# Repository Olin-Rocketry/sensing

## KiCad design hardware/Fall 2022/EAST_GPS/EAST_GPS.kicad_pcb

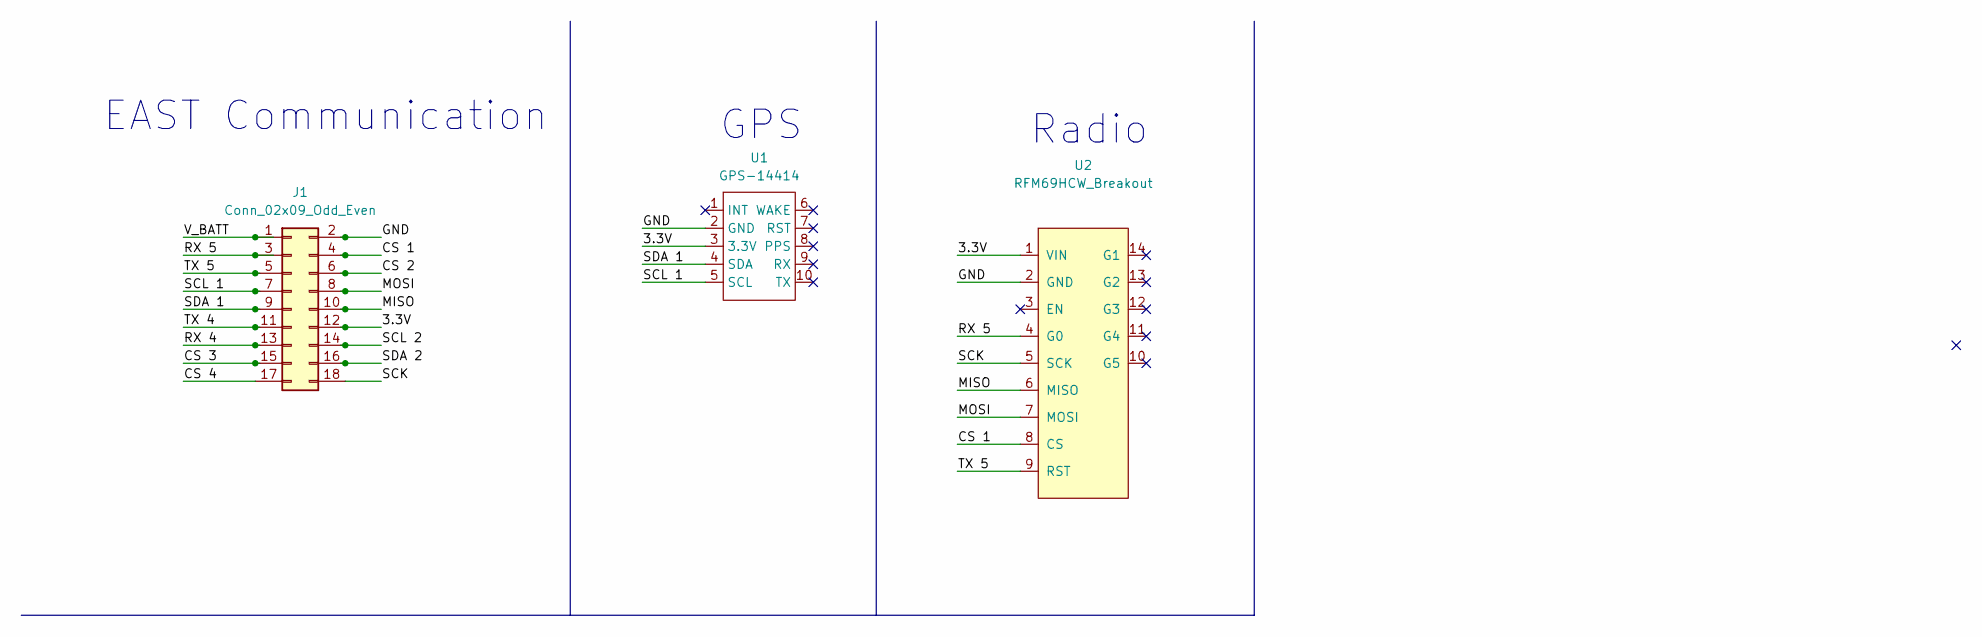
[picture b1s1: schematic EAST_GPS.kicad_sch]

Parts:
J1: Conn_02x09_Odd_Even; PinHeader_2x09_P2.54mm_Vertical
U1: GPS-14414
U2: RFM69HCW_Breakout

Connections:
/3.3V: J1.12, U1.3 (3.3V), U2.1 (VIN)
/CS 1: J1.4, U2.8 (CS)
/CS 2: J1.6
/CS 3: J1.15
/CS 4: J1.17
/GND: J1.2, U1.2 (GND), U2.2 (GND)
/MISO: J1.10, U2.6 (MISO)
/MOSI: J1.8, U2.7 (MOSI)
/RX 4: J1.13
/RX 5: J1.3, U2.4 (G0)
/SCK: J1.18, U2.5 (SCK)
/SCL 1: J1.7, U1.5 (SCL)
/SCL 2: J1.14
/SDA 1: J1.9, U1.4 (SDA)
/SDA 2: J1.16
/TX 4: J1.11
/TX 5: J1.5, U2.9 (RST)
/V_BATT: J1.1

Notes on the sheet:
EAST Communication
Radio
GPS

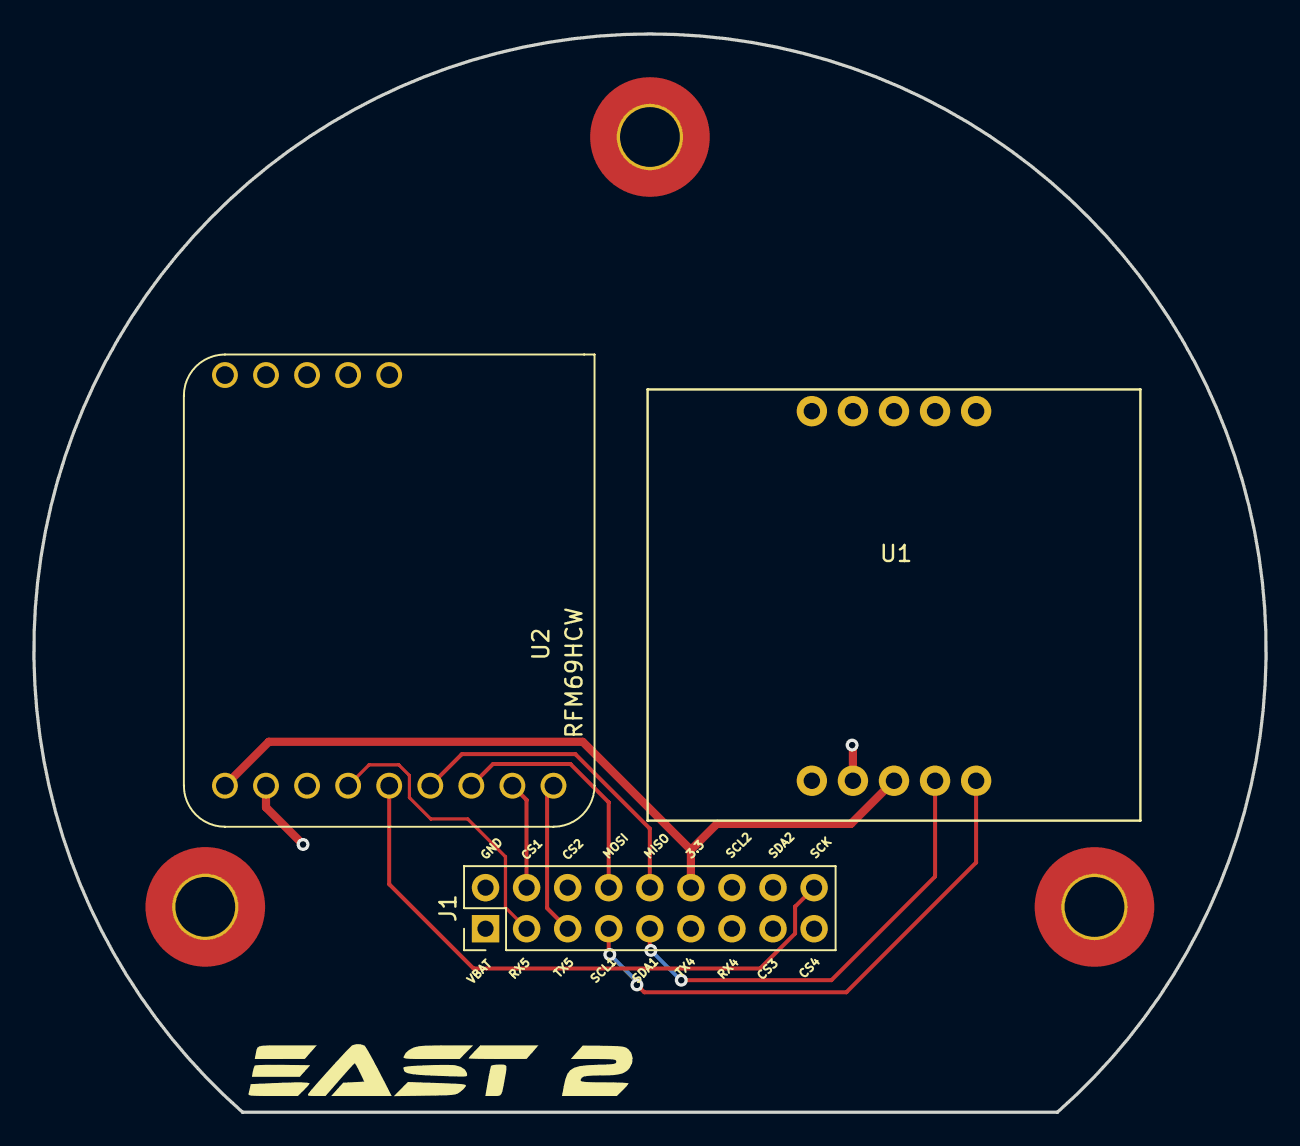
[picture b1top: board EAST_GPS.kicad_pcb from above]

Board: 2 copper layers, 76.2 x 66.7 mm, 3 parts (1 on the bottom side), 10 nets.

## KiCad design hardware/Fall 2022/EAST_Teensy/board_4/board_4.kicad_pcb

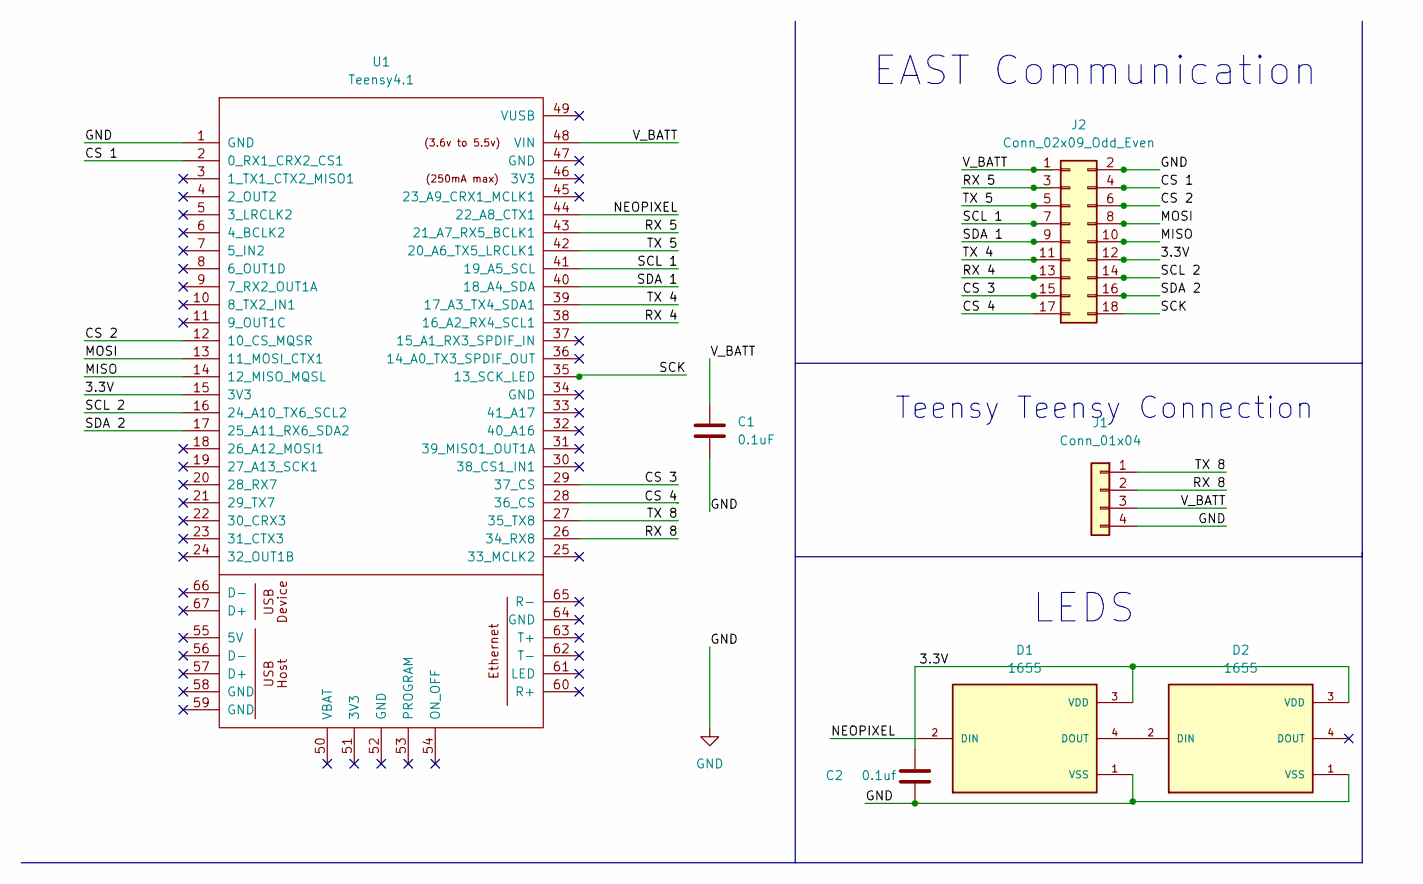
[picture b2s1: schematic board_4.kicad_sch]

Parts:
C1: 0.1uF; C_0603_1608Metric
C2: 0.1uf; C_0603_1608Metric
D1, D2: 1655; LED_1655; PARTREV 01
J1: Conn_01x04; JST_PH_S4B-PH-K_1x04_P2.00mm_Horizontal
J2: Conn_02x09_Odd_Even; PinHeader_2x09_P2.54mm_Vertical
U1: Teensy4.1; Teensy41

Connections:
/3.3V: C2.2, D1.3 (VDD), D2.3 (VDD), J2.12, U1.15 (3V3)
/CS 1: J2.4, U1.2 (0_RX1_CRX2_CS1)
/CS 2: J2.6, U1.12 (10_CS_MQSR)
/CS 3: J2.15, U1.29 (37_CS)
/CS 4: J2.17, U1.28 (36_CS)
/MISO: J2.10, U1.14 (12_MISO_MQSL)
/MOSI: J2.8, U1.13 (11_MOSI_CTX1)
/NEOPIXEL: D1.2 (DIN), U1.44 (22_A8_CTX1)
/RX 4: J2.13, U1.38 (16_A2_RX4_SCL1)
/RX 5: J2.3, U1.43 (21_A7_RX5_BCLK1)
/RX 8: J1.2, U1.26 (34_RX8)
/SCK: J2.18, U1.35 (13_SCK_LED)
/SCL 1: J2.7, U1.41 (19_A5_SCL)
/SCL 2: J2.14, U1.16 (24_A10_TX6_SCL2)
/SDA 1: J2.9, U1.40 (18_A4_SDA)
/SDA 2: J2.16, U1.17 (25_A11_RX6_SDA2)
/TX 4: J2.11, U1.39 (17_A3_TX4_SDA1)
/TX 5: J2.5, U1.42 (20_A6_TX5_LRCLK1)
/TX 8: J1.1, U1.27 (35_TX8)
/V_BATT: C1.1, J1.3, J2.1, U1.48 (VIN)
GND: C1.2, C2.1, D1.1 (VSS), D2.1 (VSS), J1.4, J2.2, U1.1 (GND)
unnamed: D1.4 (DOUT), D2.2 (DIN)

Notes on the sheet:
LEDS
Teensy Teensy Connection
EAST Communication

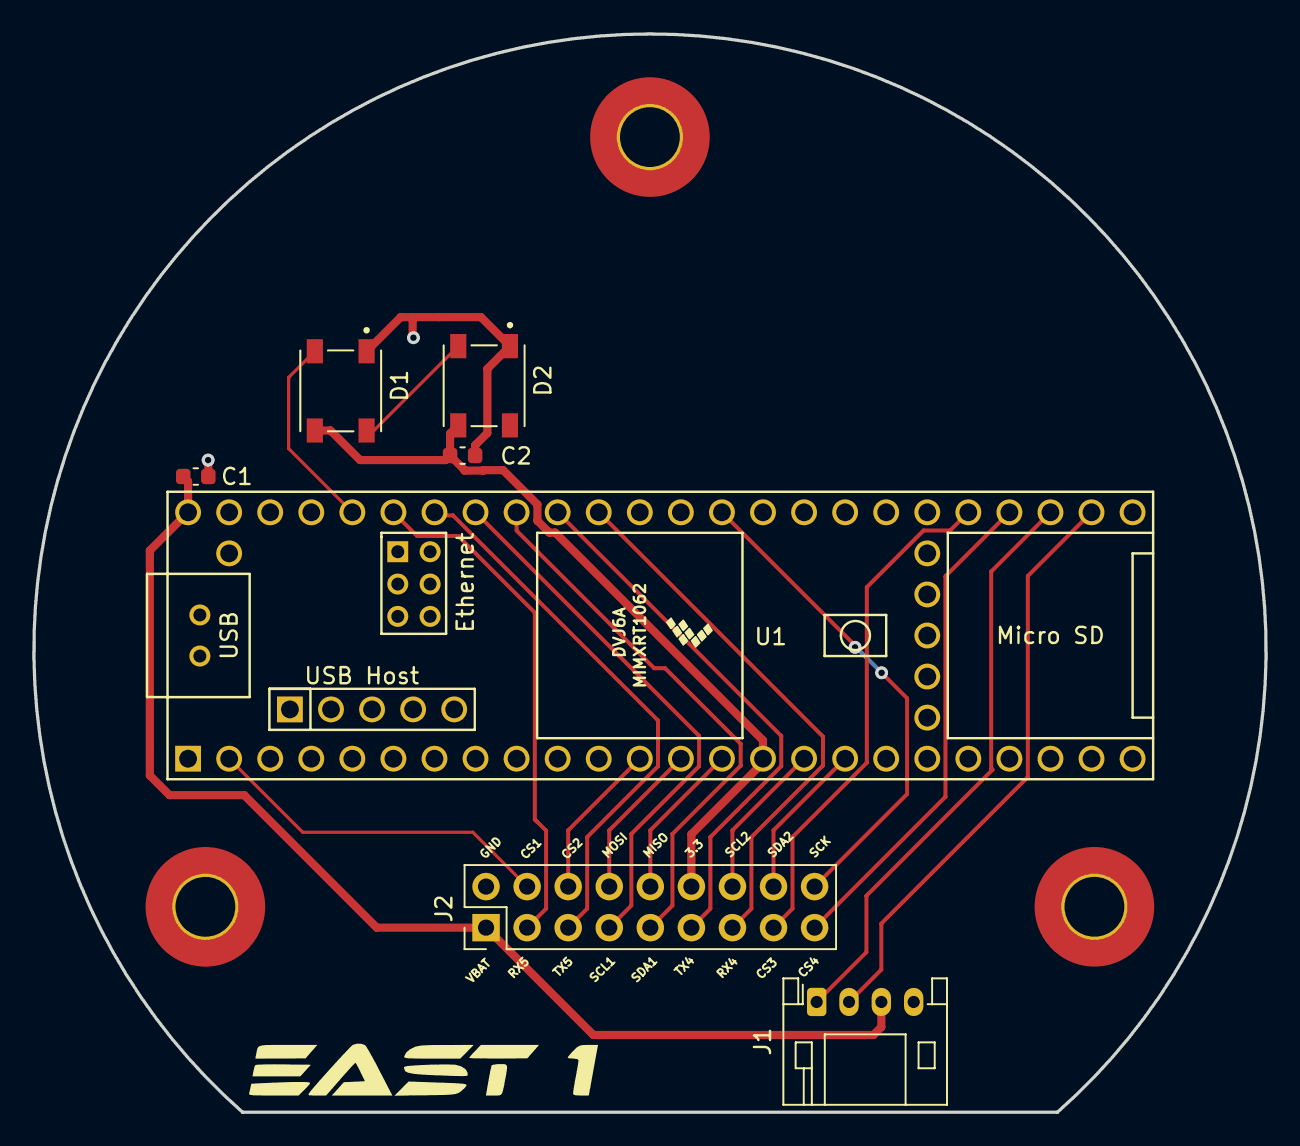
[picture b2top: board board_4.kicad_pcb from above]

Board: 2 copper layers, 76.2 x 66.7 mm, 7 parts (0 on the bottom side), 22 nets.

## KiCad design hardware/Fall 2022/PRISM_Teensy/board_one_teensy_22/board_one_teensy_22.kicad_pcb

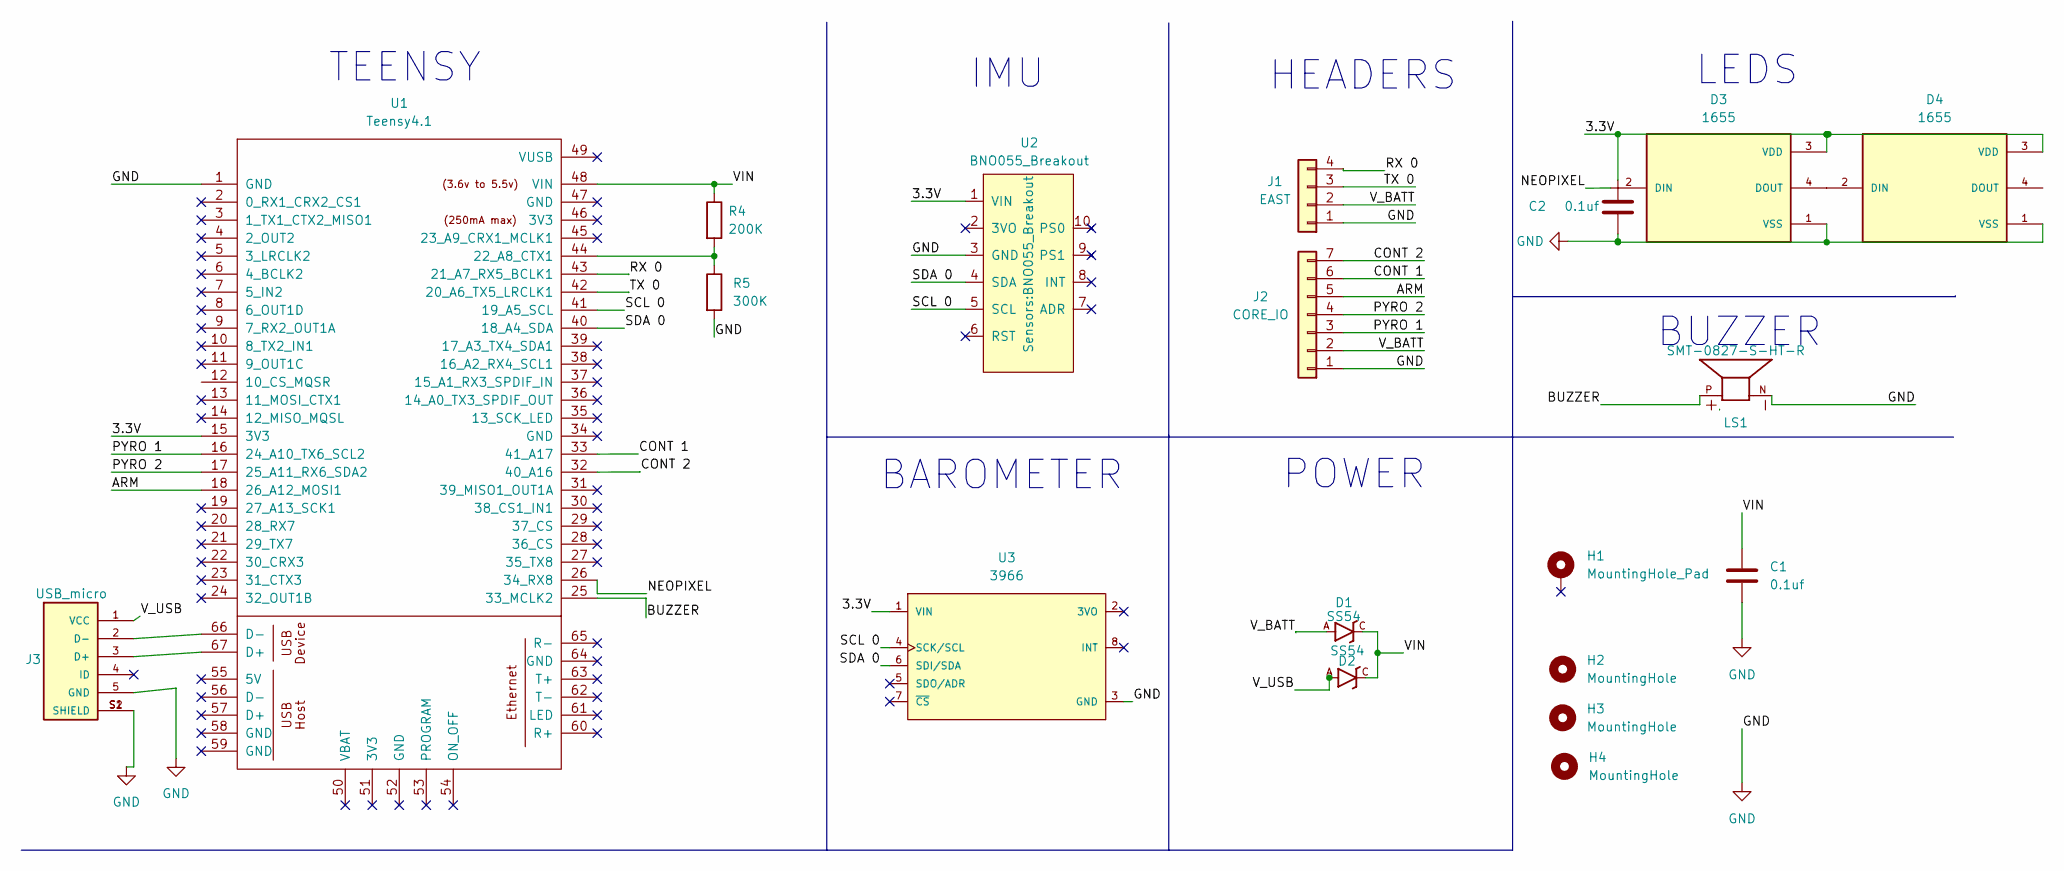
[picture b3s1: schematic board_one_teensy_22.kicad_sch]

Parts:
C1, C2: 0.1uf; C_0603_1608Metric
D1, D2: SS54; DO-214AC
D3, D4: 1655; LED_1655; PARTREV 01
H1: MountingHole_Pad; MountingHole_3.2mm_M3_DIN965_Pad_TopBottom
H2, H3, H4: MountingHole; MountingHole_3.2mm_M3_DIN965_Pad_TopBottom
J1: EAST; JST_PH_S4B-PH-K_1x04_P2.00mm_Horizontal
J2: CORE_IO; JST_PH_S7B-PH-K_1x07_P2.00mm_Horizontal
J3: USB_micro; GCT_USB3131-30-0230-A_REVB
LS1: SMT-0827-S-HT-R; XDCR_SMT-0827-S-HT-R; PARTREV 31/03/20
R4: 200K; R_0603_1608Metric
R5: 300K; R_0603_1608Metric
U1: Teensy4.1; Teensy41
U2: BNO055_Breakout
U3: 3966; Adafruit_Industries-3966-MFG; mouser part number 485-3966; digikey description BMP388 - PRECISION BAROMETRIC PR

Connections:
/3.3V: C2.2, D3.3 (VDD), D4.3 (VDD), U1.15 (3V3), U2.1 (VIN), U3.1 (VIN)
/ARM: J2.5, U1.18 (26_A12_MOSI1)
/BUZZER: LS1.P, U1.25 (33_MCLK2)
/CONT 1: J2.6, U1.33 (41_A17)
/CONT 2: J2.7, U1.32 (40_A16)
/NEOPIXEL: D3.2 (DIN), U1.26 (34_RX8)
/PYRO 1: J2.3, U1.16 (24_A10_TX6_SCL2)
/PYRO 2: J2.4, U1.17 (25_A11_RX6_SDA2)
/RX 0: J1.4, U1.43 (21_A7_RX5_BCLK1)
/SCL 0: U1.41 (19_A5_SCL), U2.5 (SCL), U3.4 (SCK/SCL)
/SDA 0: U1.40 (18_A4_SDA), U2.4 (SDA), U3.6 (SDI/SDA)
/TX 0: J1.3, U1.42 (20_A6_TX5_LRCLK1)
/VIN: C1.1, D1.C, D2.C, R4.1, U1.48 (VIN)
/V_BATT: D1.A, J1.2, J2.2
/V_USB: D2.A, J3.1 (VCC)
GND: C1.2, C2.1, D3.1 (VSS), D4.1 (VSS), J1.1, J2.1, J3.5 (GND), J3.S1 (SHIELD), J3.S2 (SHIELD), LS1.N, R5.2, U1.1 (GND), U2.3 (GND), U3.3 (GND)
unnamed: D3.4 (DOUT), D4.2 (DIN)
unnamed: J3.2 (D-), U1.66 (D-)
unnamed: J3.3 (D+), U1.67 (D+)
unnamed: R4.2, R5.1, U1.44 (22_A8_CTX1)

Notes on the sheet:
BUZZER
TEENSY
HEADERS
POWER
LEDS
IMU
BAROMETER

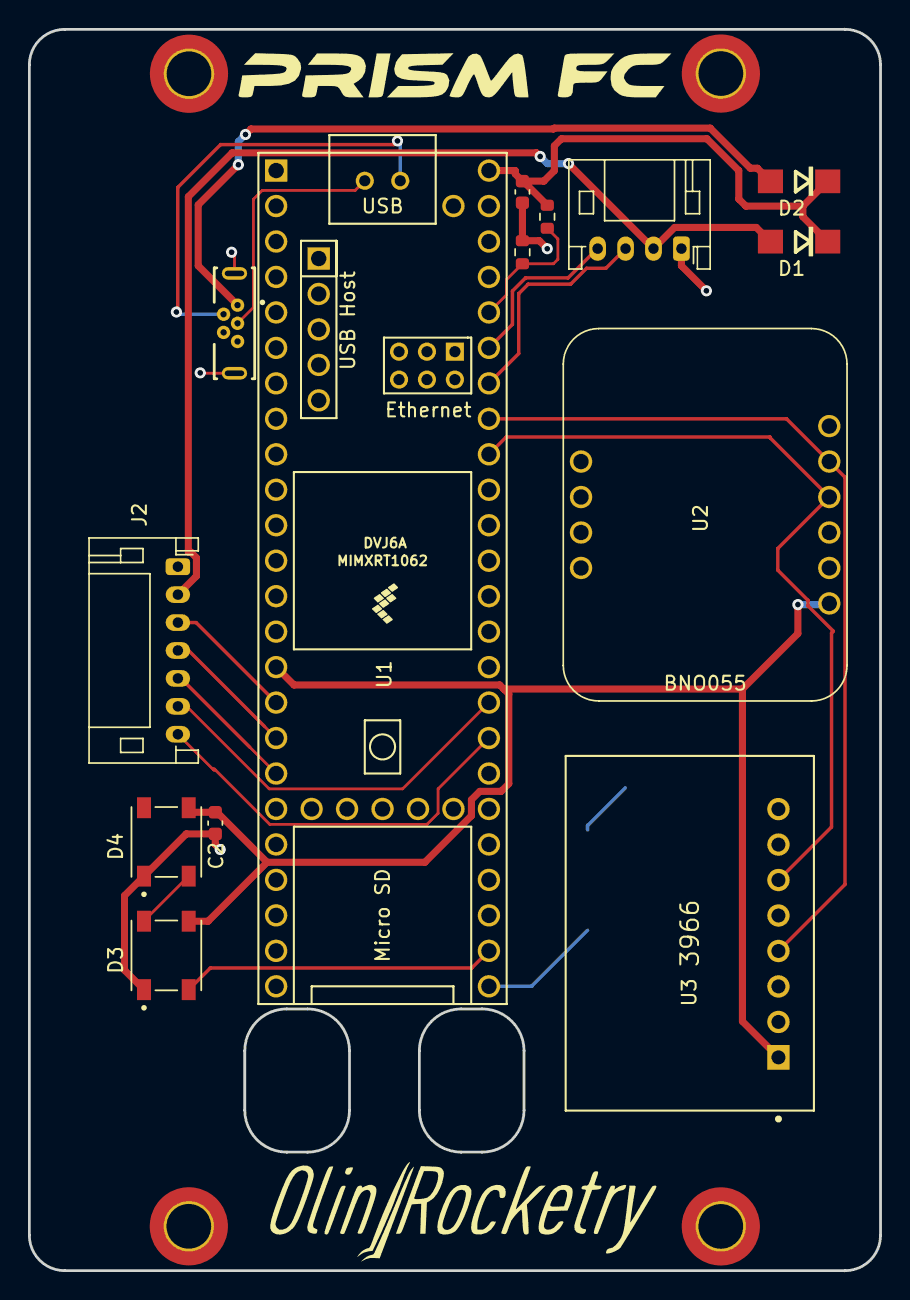
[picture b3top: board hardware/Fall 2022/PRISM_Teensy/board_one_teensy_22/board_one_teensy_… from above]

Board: 2 copper layers, 61.0 x 88.9 mm, 19 parts (1 on the bottom side), 20 nets.

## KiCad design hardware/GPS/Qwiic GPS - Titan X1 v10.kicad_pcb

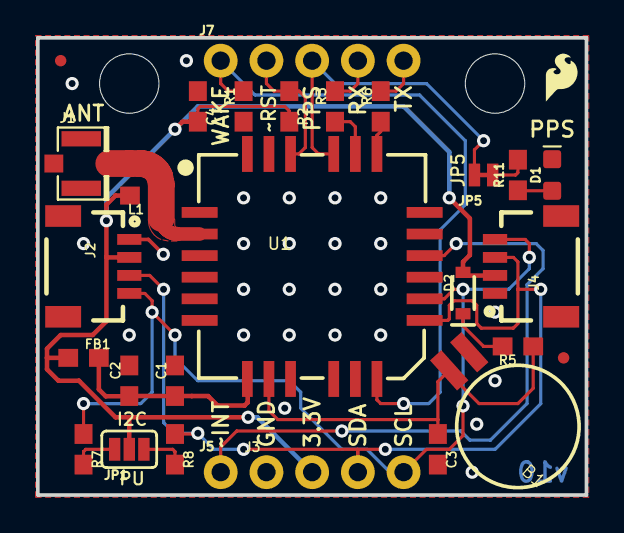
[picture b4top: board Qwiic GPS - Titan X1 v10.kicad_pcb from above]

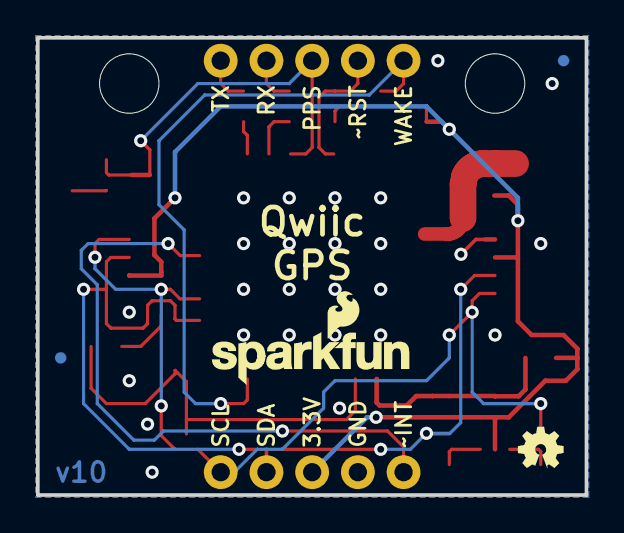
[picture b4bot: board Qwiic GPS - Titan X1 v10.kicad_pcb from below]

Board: 2 copper layers, 30.5 x 25.4 mm, 38 parts (4 on the bottom side), 20 nets.

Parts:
B1: 6.8MM_COIN_CELL; BATTCON-6.8MM
C1: 0.1uF; 0603
C2, C3, C4: 1.0uF; 0603
D1: BLUE; LED-0603
D2: 0.5A/40V/420mV; SOD-323
FB1: 600Ohm/100MHz; 0603
FRAME1: FRAME-LETTER; CREATIVE_COMMONS
J1: U.FL
J2, J4: Qwiic Right Angle; 1X04_1MM_RA
J3: PTH; 1X04_NO_SILK
J5: 1X01_NO_SILK
J7: 1X05_NO_SILK
JP1: SMT-JUMPER_3_2-NC_PASTE_SILK
JP2, JP6, JP7, JP8: FIDUCIALUFIDUCIAL; MICRO-FIDUCIAL
JP3, JP4: STAND-OFF
JP5: SMT-JUMPER_2_NC_TRACE_NO-SILK
L1: 33nH/±5%/500mA; 0603
LOGO1: OSHW-LOGOMINI; OSHW-LOGO-MINI
LOGO2: SFE_LOGO_NAME_FLAME.1_INCH; SFE_LOGO_NAME_FLAME_.1
LOGO3: REVISION
R1, R2: 10k; 0603
R3, R6, R11: 470; 0603
R5: 1k; 0603
R7, R8: 4.7k; 0603
U1: Titan X1 GPS; TITAN_X1_GPS
U$2: SFE_LOGO_FLAME_.1
U$3: SPECIAL_INSTRUCTIONS-PRODUCTION; PRODUCTION_INSTRUCTIONS

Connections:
3.3V: C4.2, D2.A, FB1.1, J2.2, J3.2, J4.2, JP1.2, L1.2, R2.2
BACKUP: B1.+, C3.1, R5.1, U1.8
EXT_ANT: J1.FEED, L1.1, U1.2
GND: B1.-, C1.2, C2.2, C3.2, C4.1, D1.C, J1.1, J1.2, J2.1, J3.1, J4.1, R1.1, U1.1, U1.3, U1.4, U1.5, U1.6, U1.9, U1.10, U1.11, U1.24
INT: J5.1, U1.16
unnamed: D1.A, R11.1
unnamed: JP5.1, R11.2
unnamed: JP1.1, R8.2
unnamed: D2.C, R5.2
unnamed: JP1.3, R7.2
PPS: J7.3, JP5.2, U1.21
RX: J7.4, R3.2
RXLV: R3.1, U1.20
SCL: J2.4, J3.4, J4.4, R7.1, U1.14
SDA: J2.3, J3.3, J4.3, R8.1, U1.13
TX: J7.5, R6.2
TXLV: R6.1, U1.19
VCC_FILTERED: C1.1, C2.1, FB1.2, U1.7
WAKE: J7.1, R1.2, U1.12
~RESET: J7.2, R2.1, U1.22

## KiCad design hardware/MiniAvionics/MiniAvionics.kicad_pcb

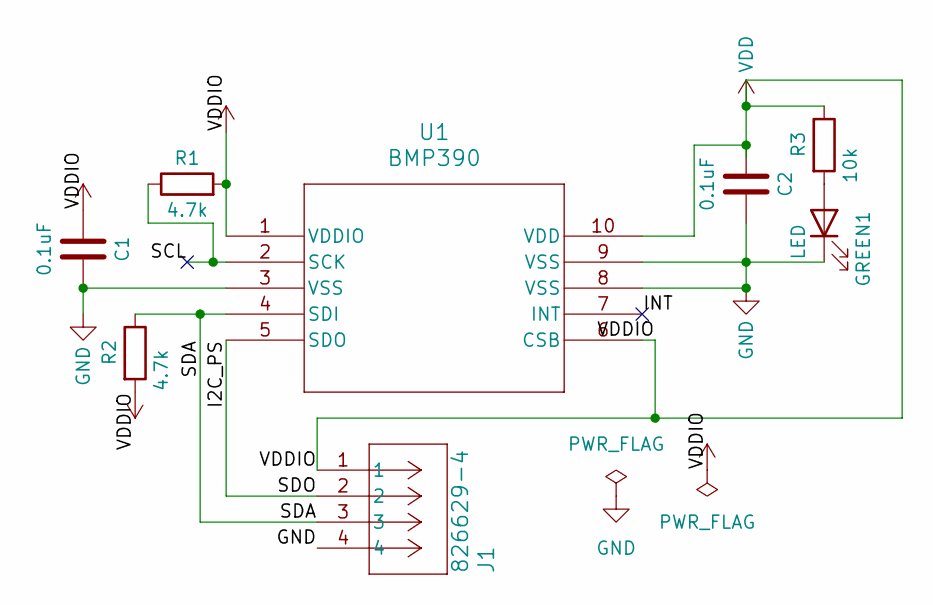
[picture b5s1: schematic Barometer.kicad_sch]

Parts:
C1, C2: 0.1uF; R_0603_1608Metric
GREEN1: LED; R_0603_1608Metric
J1: 826629-4; CON4_1X4_P100UM_HDR2_TYC
R1, R2: 4.7k; R_0603_1608Metric
R3: 10k; R_0603_1608Metric
U1: BMP390; LGA10_BMP390_BOS-L

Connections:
/BMP390/I2C_PS: J1.2, U1.5 (SDO)
/BMP390/INT: U1.7 (INT)
/BMP390/SCL: R1.1, U1.2 (SCK)
/BMP390/SDA: J1.3, R2.1, U1.4 (SDI)
GND: C1.2, C2.2, GREEN1.1 (K), J1.4, U1.3 (VSS), U1.8 (VSS), U1.9 (VSS)
unnamed: GREEN1.2 (A), R3.2
VDD: C1.1, C2.1, J1.1, R1.2, R2.2, R3.1, U1.1 (VDDIO), U1.6 (CSB), U1.10 (VDD)

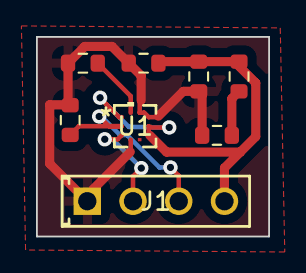
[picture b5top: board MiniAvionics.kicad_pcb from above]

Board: 2 copper layers, 12.9 x 11.1 mm, 8 parts (0 on the bottom side), 6 nets.

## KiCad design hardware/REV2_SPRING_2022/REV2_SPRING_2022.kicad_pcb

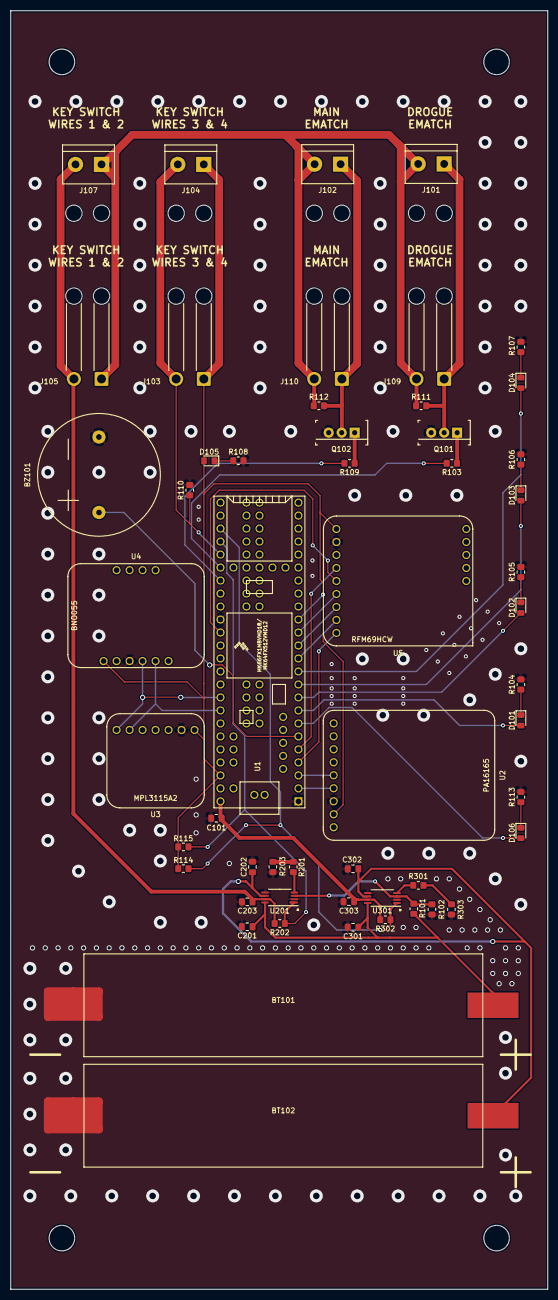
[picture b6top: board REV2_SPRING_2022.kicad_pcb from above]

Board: 2 copper layers, 105.0 x 250.0 mm, 54 parts (0 on the bottom side), 43 nets.

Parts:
BT101, BT102: Battery_Cell; MyBatteryHolder_MPD_BH-18650-PC2
BZ101: Buzzer; Large_Buzzer_24mmOD_14.8mmPinDistance_1.0mmPinDiameter
C101, C201, C202, C203, C301, C302, C303: C_0.1u; C_0805_2012Metric_Pad1.18x1.45mm_HandSolder
D101, D102, D103, D104, D105, D106: LED; LED_0805_2012Metric_Pad1.15x1.40mm_HandSolder
J101, J102, J104, J107: Screw_Terminal_01x02; TerminalBlock_bornier-2_P5.08mm
J103, J105, J109, J110: Conn_01x02_Female; SolderWire-1sqmm_1x02_P5.4mm_D1.4mm_OD2.7mm_Relief2x
Q101, Q102: Q_NMOS_GDS; TO-220-3
R101: R_15k; R_0805_2012Metric_Pad1.20x1.40mm_HandSolder
R102: R_4.7k; R_0805_2012Metric_Pad1.20x1.40mm_HandSolder
R103, R109, R110, R111, R112, R114, R115, R202, R302: R_10k; R_0805_2012Metric_Pad1.20x1.40mm_HandSolder
R104, R105, R106, R107, R108, R113: R_750; R_0805_2012Metric_Pad1.20x1.40mm_HandSolder
R201, R203, R301, R303: R_200; R_0805_2012Metric_Pad1.20x1.40mm_HandSolder
U1: Teensy3.6_All_Pins; Teensy35_36_All_Pins
U2: PA16165_Breakout
U3: MPL3115A2_Breakout
U4: BNO055_Breakout
U5: RFM69HCW_Breakout
U201, U301: TPS2113ADRBR; TSSOP-8_4.4x3mm_P0.65mm

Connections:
/3.3V: D105.2, J103.1, J104.1, R114.1, R115.1, U1.15, U1.51, U2.8, U3.1, U4.1, U5.1
/BAT1: BT101.1, C201.1, C301.1, R101.1, U201.8, U301.8
/BAT2: BT102.1, C202.1, C302.1, U201.6, U301.6
/BUZZER: BZ101.1, U1.6
/CS0: U1.12, U5.8
/E-MATCH_TRIGGER_1: R103.2, U1.35
/E-MATCH_TRIGGER_2: R109.2, U1.36
/EMATCH_1+: J101.1, J109.1, Q101.2, R111.2
/EMATCH_2+: J102.1, J110.1, Q102.2, R112.2
/KEY_SWITCH_DIGITAL: J103.2, J104.2, R110.1, U1.34
/LED_0: D106.2, U1.7
/LED_1: D101.2, U1.8
/LED_2: D102.2, U1.9
/LED_3: D103.2, U1.10
/LED_4: D104.2, U1.11
/MISO0: U1.14, U5.6
/MOSI0: U1.13, U5.7
/PWM: U1.4, U5.9
/RX1: U1.2, U2.6
/SCK: U1.40, U5.5
/SCL0: U1.46, U3.6, U4.5
/SCL2: U1.5, U5.4
/SDA0: U1.45, U3.7, U4.4
/TPS2113A for E-match/VSNS: R101.2, R102.1, U201.3, U301.3
/TPS_1_STAT: R114.2, R302.2, U1.32, U301.1
/TPS_2_STAT: R115.2, R202.2, U1.33, U201.1
/TX1: U1.3, U2.5
/V_EMATCH: J101.2, J102.2, J105.1, J107.1, J109.2, J110.2, R111.1, R112.1
/V_EMATCH_TO_KEY_SWITCH: C203.1, J105.2, J107.2, R202.1, U201.7
/V_TEENSY: C101.1, C303.1, R302.1, U1.53, U301.7
GND: BT101.2, BT102.2, BZ101.2, C101.2, C201.2, C202.2, C203.2, C301.2, C302.2, C303.2, Q101.3, Q102.3, R102.2, R104.2, R105.2, R106.2, R107.2, R108.2, R110.2, R113.2, R203.1, R303.1, U1.1, U1.39, U2.7, U3.2, U4.3, U5.2, U201.2, U201.5, U301.2, U301.5
unnamed: D101.1, R104.1
unnamed: D102.1, R105.1
unnamed: D103.1, R106.1
unnamed: D104.1, R107.1
unnamed: D105.1, R108.1
unnamed: D106.1, R113.1
unnamed: Q101.1, R103.1
unnamed: Q102.1, R109.1
unnamed: R201.1, R203.2
unnamed: R201.2, U201.4
unnamed: R301.1, R303.2
unnamed: R301.2, U301.4

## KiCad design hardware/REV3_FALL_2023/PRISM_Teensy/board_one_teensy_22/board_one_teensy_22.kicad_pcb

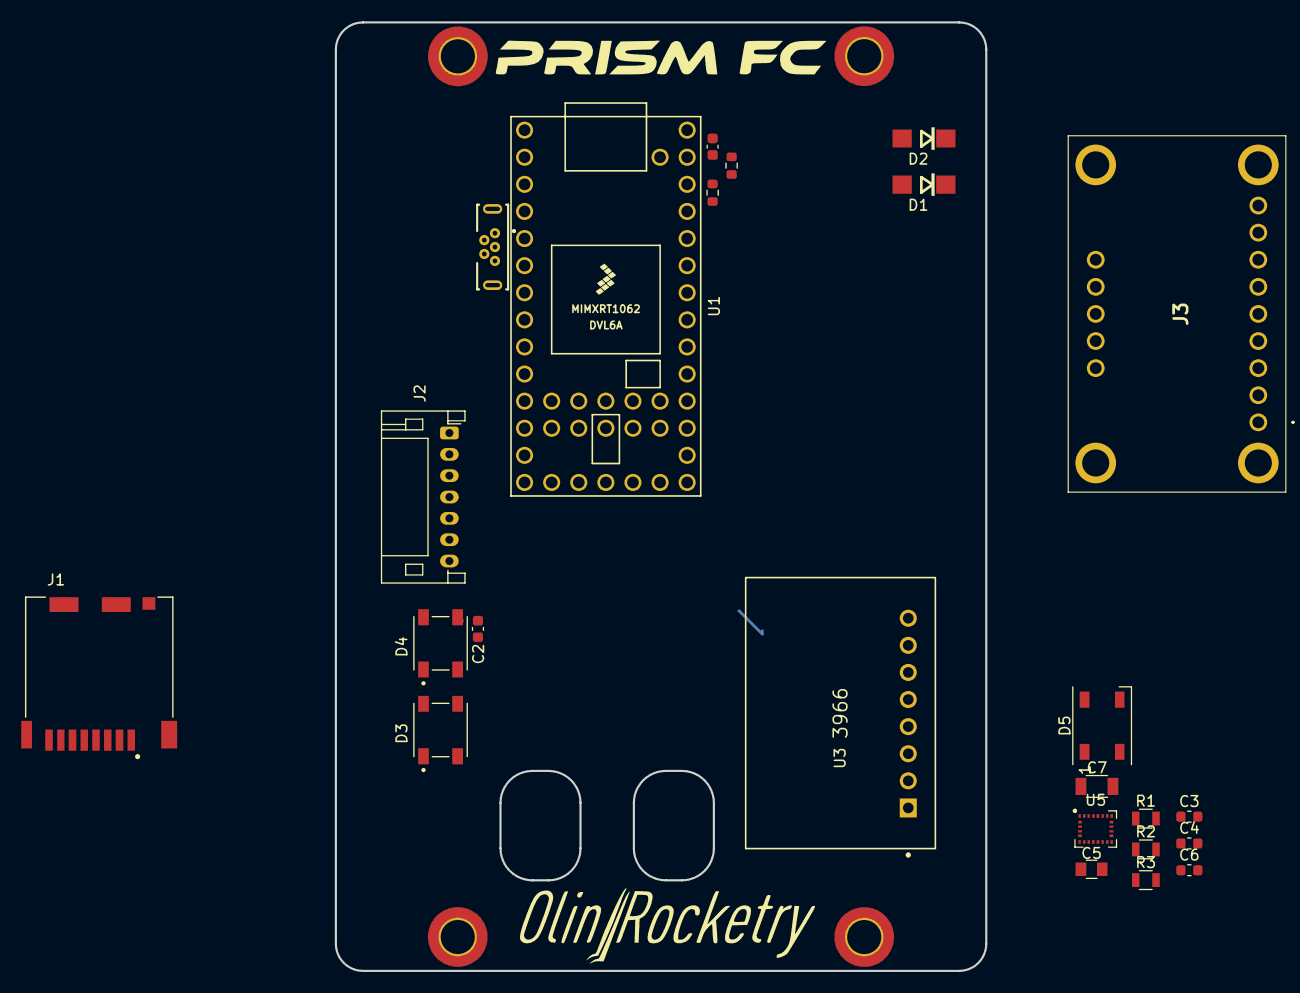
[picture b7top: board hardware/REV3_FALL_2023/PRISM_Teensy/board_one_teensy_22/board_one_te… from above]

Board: 2 copper layers, 61.0 x 88.9 mm, 29 parts (1 on the bottom side), 19 nets.

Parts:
C1, C2: 0.1uf; C_0603_1608Metric
C3, C4, C6: C_100nF; C_0603_1608Metric
C5: C_10uF; C_0805_OEM
C7: C_10nF; C_1206_OEM
D1, D2: SS54; DO-214AC
D3, D4: 1655; LED_1655
D5: WS2812B; LED_WS2812B_PLCC4_5.0x5.0mm_P3.2mm
H1: MountingHole_Pad; MountingHole_3.2mm_M3_DIN965_Pad_TopBottom
H2, H3, H4: MountingHole; MountingHole_3.2mm_M3_DIN965_Pad_TopBottom
J1: DM3CS-SF; HRS_DM3CS-SF
J2: CORE_IO; JST_PH_S7B-PH-K_1x07_P2.00mm_Horizontal
J3: 3387
J3#2: USB_micro; GCT_USB3131-30-0230-A_REVB
LS1: SMT-0827-S-HT-R; XDCR_SMT-0827-S-HT-R
R1, R2, R3: R_10K; R_0805_OEM
R4: 200K; R_0603_1608Metric
R5: 300K; R_0603_1608Metric
U1: Teensy4.0; Teensy40
U3: 3966; Adafruit_Industries-3966-MFG
U5: LSM9DS1; LGA-24L_3x3.5mm_P0.43mm

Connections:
/3.3V: C3.2, C4.2, C5.1, J1.4 (VDD), J3.2 (3V3), R1.1, R2.1, R3.1, U1.31 (3V3), U3.1 (VIN), U5.1 (VDDIO), U5.3 (VDDIO), U5.22 (VDD), U5.23 (VDD)
/5V: C2.2, D3.3 (VDD), D4.3 (VDD), U1.33 (VIN)
/ARM: J2.5, U1.37 (26_A12_MOSI1)
/BUZZER: LS1.P, U1.18 (PROGRAM)
/CONT 1: J2.6, U1.27 (20_A6_TX5_LRCLK1)
/CONT 2: J2.7, U1.28 (21_A7_RX5_BCLK1)
/PYRO 1: J2.3, U1.35 (24_A10_TX6_SCL2)
/PYRO 2: J2.4, U1.36 (25_A11_RX6_SDA2)
/SCL 0: J3.4 (SCL), R1.2, U1.26 (19_A5_SCL0), U3.4 (SCK/SCL), U5.2 (SCL/SPC)
/SDA 0: J3.5 (SDA), R2.2, U1.25 (18_A4_SDA0), U3.6 (SDI/SDA), U5.4 (SDA/SDI/SDO), U5.6 (SDO_M)
/VIN: C1.1, D1.C, D2.C, R4.1
/V_BATT: D1.A, J2.2
/V_USB: D2.A, J3#2.1 (VCC)
GND: C1.2, C2.1, C3.1, C4.1, C5.2, C6.2, C7.2, D3.1 (VSS), D4.1 (VSS), J1.S1 (GND), J1.S2 (GND), J1.S3 (GND), J1.S5 (GND), J2.1, J3.3 (GND), J3#2.5 (GND), J3#2.S1 (SHIELD), J3#2.S2 (SHIELD), LS1.N, R5.2, U1.1 (GND), U1.32 (GND), U3.3 (GND), U5.14 (RES), U5.15 (RES), U5.16 (RES), U5.17 (RES), U5.18 (RES), U5.19 (GND), U5.20 (GND)
unnamed: D3.4 (DOUT), D4.2 (DIN)
unnamed: R4.2, R5.1
unnamed: C6.1, U5.24 (C1)
unnamed: C7.1, U5.21 (CAP)
unnamed: R3.2, U5.13 (DEN_A/G)

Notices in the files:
parts and their libraries:
HTTPS://CREATIVECOMMONS.ORG/LICENSES/BY-SA/4.0
RELEASED UNDER THE CREATIVE COMMONS ATTRIBUTION SHARE-ALIKE 4.0 LICENSE
